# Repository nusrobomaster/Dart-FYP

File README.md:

# 🎯 FYP Dart Launcher (RoboMaster Competition)

This repository hosts the STM32 firmware for our Final Year Project (FYP), which focuses on building the **dart launcher subsystem** for the NUS RoboMaster competition robot. The project is developed and maintained using **STM32CubeIDE** with the DEV A environment, ensuring consistent toolchain and configuration across all team members.

## 🚀 Getting Started (STM32CubeIDE + DEV BOARD A)
Clone this repo and set this repo as your Workspace in stm32cubeide

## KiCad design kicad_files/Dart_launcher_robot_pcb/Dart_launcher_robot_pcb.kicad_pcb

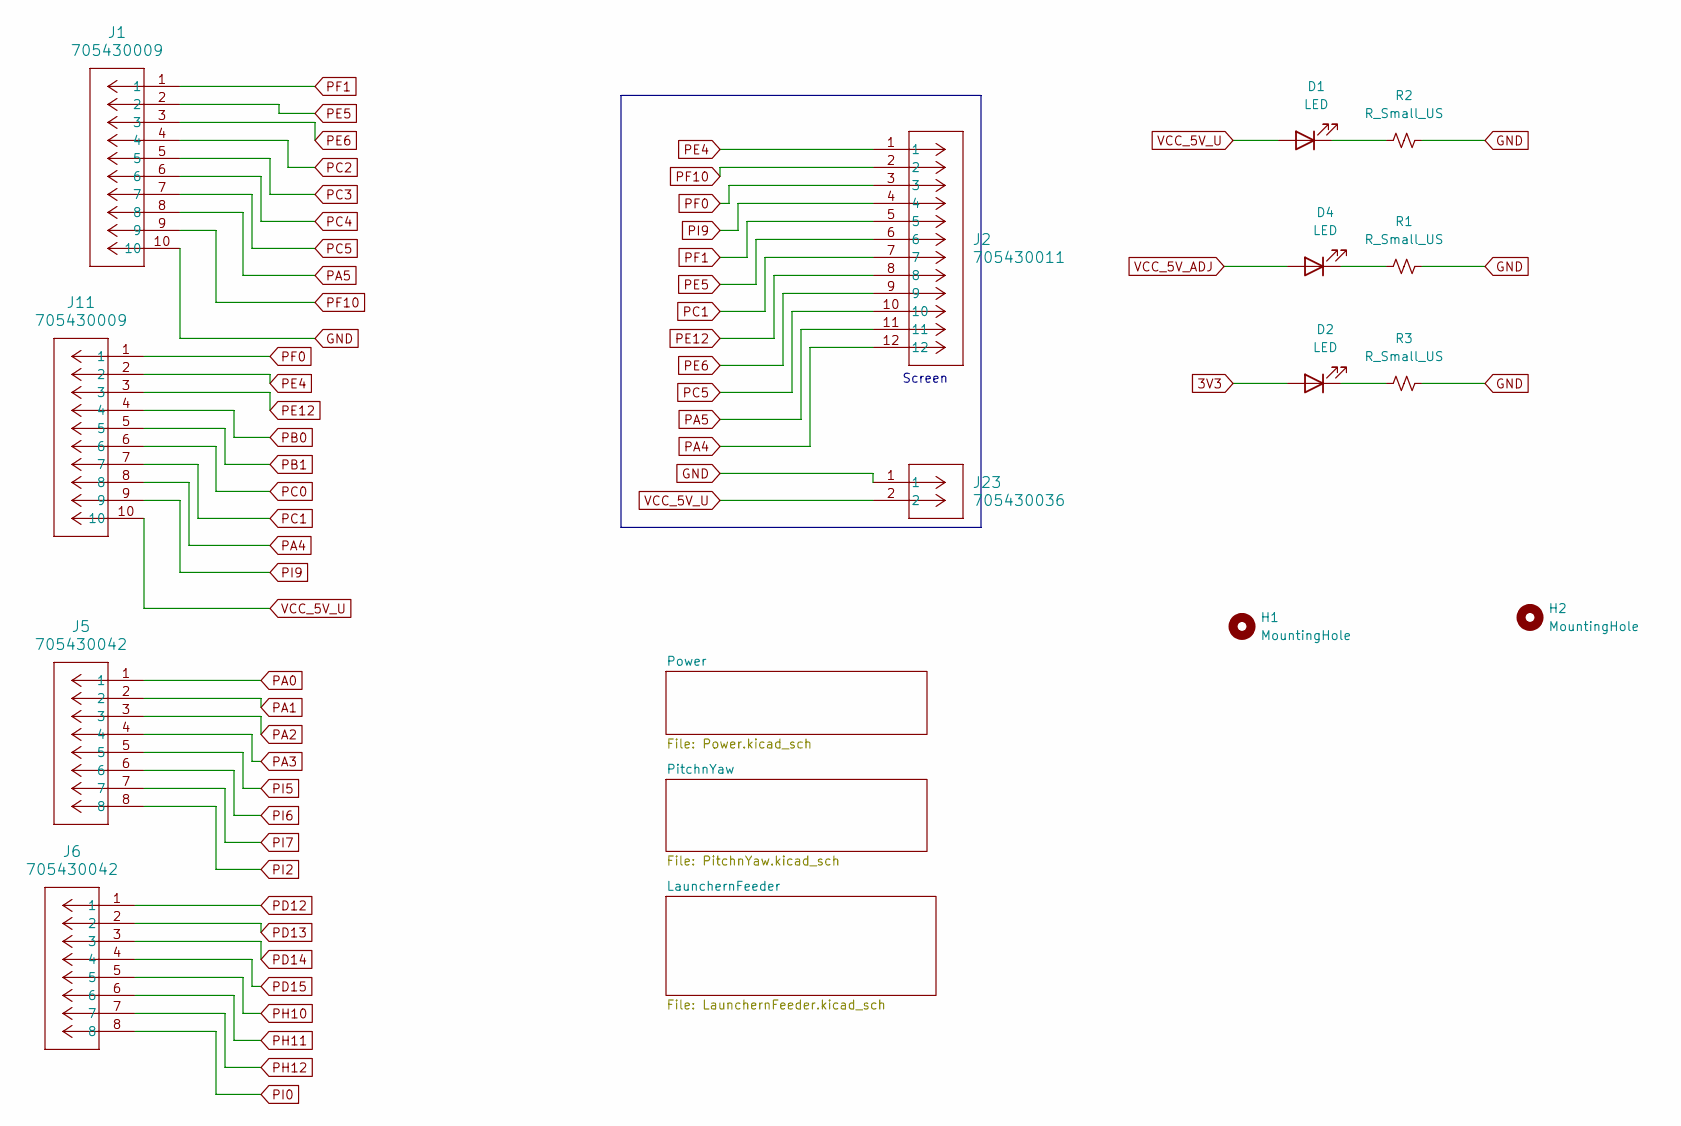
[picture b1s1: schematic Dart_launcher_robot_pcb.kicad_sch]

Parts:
D1, D2, D4: LED; LED_0805_2012Metric_Pad1.15x1.40mm_HandSolder
H1, H2: MountingHole; MountingHole_3.2mm_M3
J1, J11: 705430009; CONN_SDA-70543-xxxx_10_MOL
J2: 705430011; CONN_SDA-70543-xxxx_12_MOL
J5, J6: 705430042; CONN_SDA-70543-xxxx_08_MOL
J23: 705430036; CONN_SDA-70543-xxxx_02_MOL
R1, R2, R3: R_Small_US; R_0603_1608Metric_Pad0.98x0.95mm_HandSolder

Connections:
3V3: D2.2 (A); also elsewhere on the board
GND: J1.10, J23.1, R1.2, R2.2, R3.2; also elsewhere on the board
unnamed: D1.1 (K), R2.1
unnamed: D2.1 (K), R3.1
unnamed: D4.1 (K), R1.1
PA0: J5.1; also elsewhere on the board
PA1: J5.2; also elsewhere on the board
PA2: J5.3; also elsewhere on the board
PA3: J5.4; also elsewhere on the board
PA4: J2.12, J11.8
PA5: J1.8, J2.11
PB0: J11.4; also elsewhere on the board
PB1: J11.5; also elsewhere on the board
PC0: J11.6; also elsewhere on the board
PC1: J2.7, J11.7
PC2: J1.4
PC3: J1.5; also elsewhere on the board
PC4: J1.6; also elsewhere on the board
PC5: J1.7, J2.10
PD12: J6.1; also elsewhere on the board
PD13: J6.2; also elsewhere on the board
PD14: J6.3; also elsewhere on the board
PD15: J6.4; also elsewhere on the board
PE4: J2.1, J11.2
PE5: J1.2, J2.6
PE6: J1.3, J2.9
PE12: J2.8, J11.3
PF0: J2.3, J11.1
PF1: J1.1, J2.5
PF10: J1.9, J2.2
PH10: J6.5
PH11: J6.6
PH12: J6.7; also elsewhere on the board
PI0: J6.8; also elsewhere on the board
PI2: J5.8
PI5: J5.5; also elsewhere on the board
PI6: J5.6
PI7: J5.7
PI9: J2.4, J11.9
VCC_5V_ADJ: D4.2 (A); also elsewhere on the board
VCC_5V_U: D1.2 (A), J11.10, J23.2

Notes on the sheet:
Screen

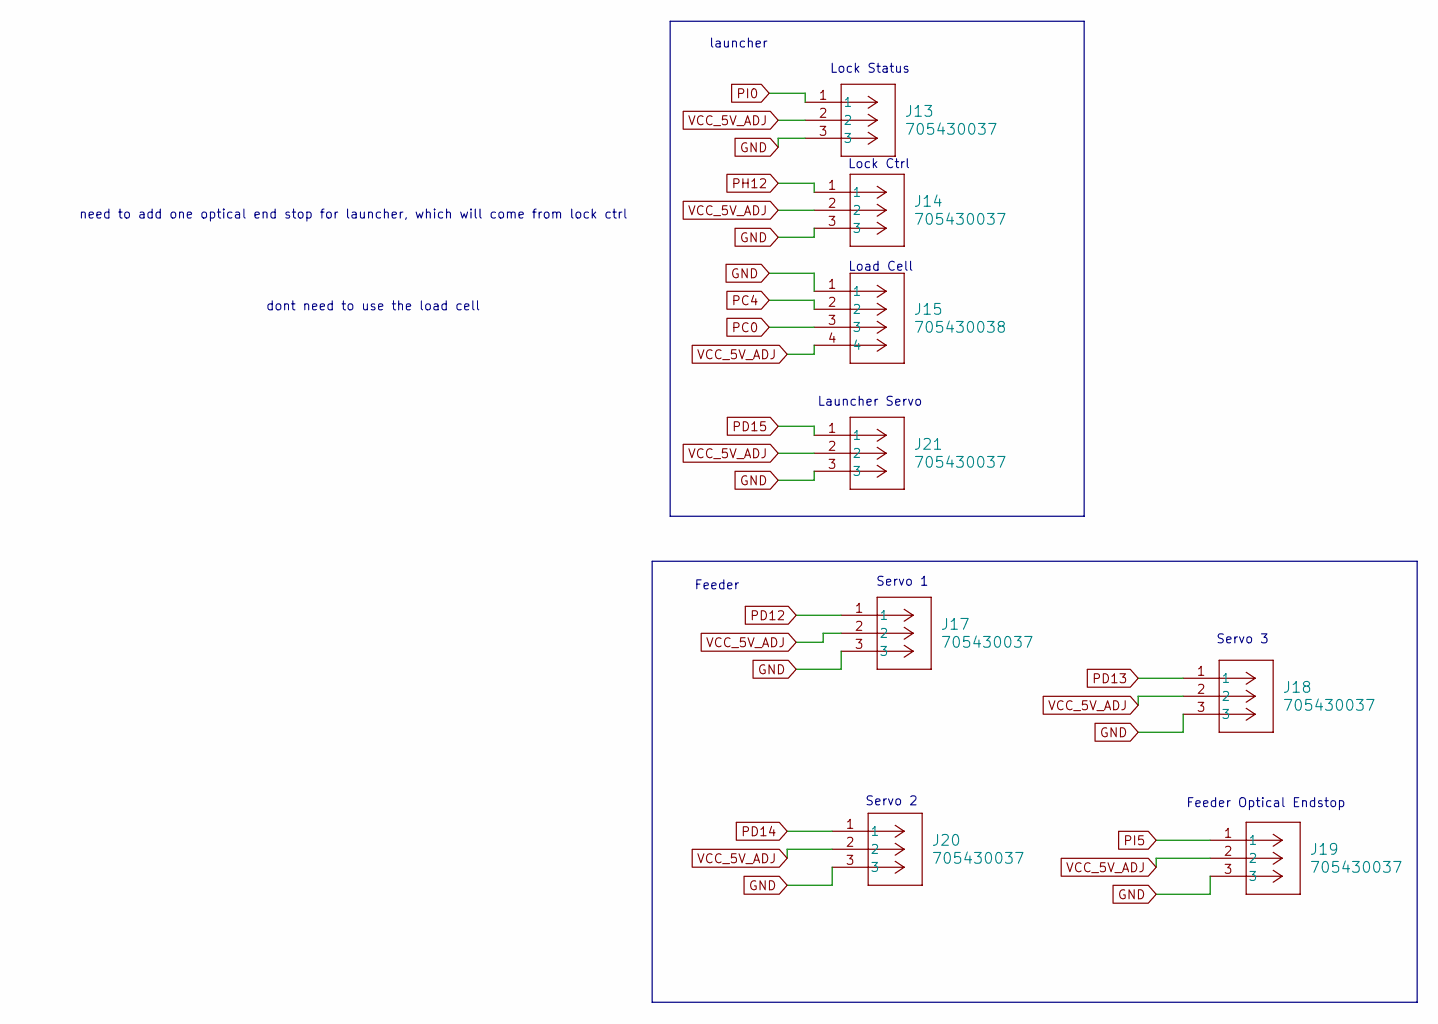
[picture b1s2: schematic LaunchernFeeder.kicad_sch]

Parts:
J13, J14, J17, J18, J19, J20, J21: 705430037; CONN_SDA-70543-xxxx_03_MOL
J15: 705430038; CONN_SDA-70543-xxxx_04_MOL

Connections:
GND: J13.3, J14.3, J15.1, J17.3, J18.3, J19.3, J20.3, J21.3; also elsewhere on the board
PC0: J15.3; also elsewhere on the board
PC4: J15.2; also elsewhere on the board
PD12: J17.1; also elsewhere on the board
PD13: J18.1; also elsewhere on the board
PD14: J20.1; also elsewhere on the board
PD15: J21.1; also elsewhere on the board
PH12: J14.1; also elsewhere on the board
PI0: J13.1; also elsewhere on the board
PI5: J19.1; also elsewhere on the board
VCC_5V_ADJ: J13.2, J14.2, J15.4, J17.2, J18.2, J19.2, J20.2, J21.2; also elsewhere on the board

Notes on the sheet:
Launcher Servo
Lock Ctrl
Servo 3
need to add one optical end stop for launcher, which will come from lock ctrl
launcher
Lock Status
Feeder
Servo 2
dont need to use the load cell
Load Cell
Servo 1
Feeder Optical Endstop

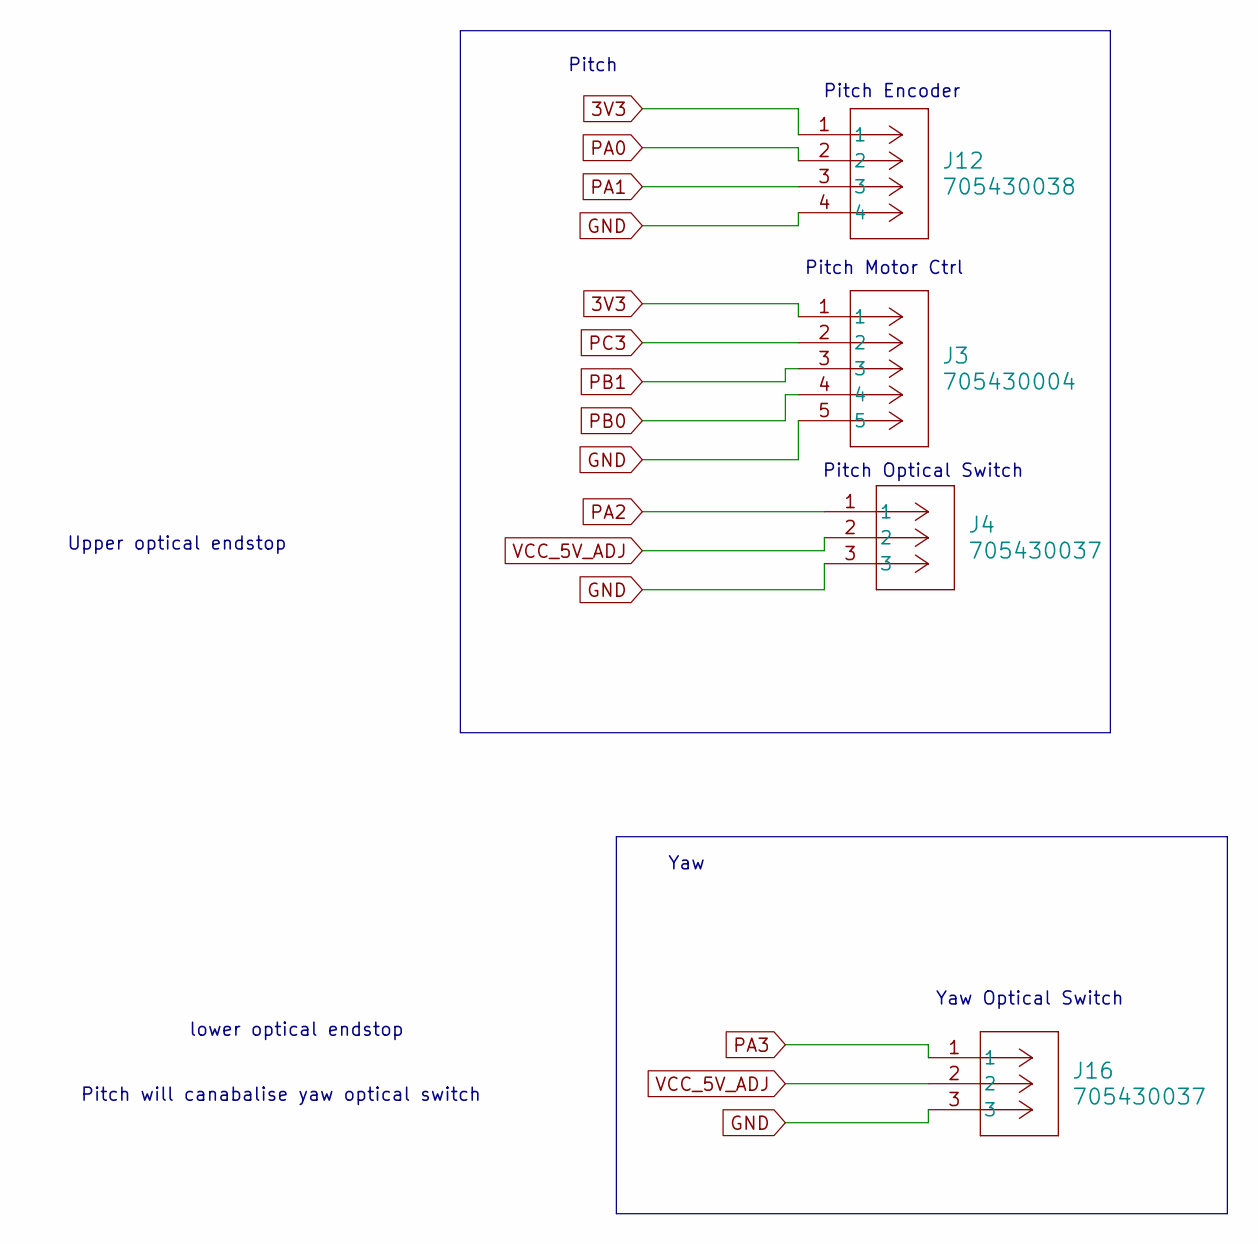
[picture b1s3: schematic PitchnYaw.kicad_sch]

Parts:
J3: 705430004; CONN_SDA-70543-xxxx_05_MOL
J4, J16: 705430037; CONN_SDA-70543-xxxx_03_MOL
J12: 705430038; CONN_SDA-70543-xxxx_04_MOL

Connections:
3V3: J3.1, J12.1; also elsewhere on the board
GND: J3.5, J4.3, J12.4, J16.3; also elsewhere on the board
PA0: J12.2; also elsewhere on the board
PA1: J12.3; also elsewhere on the board
PA2: J4.1; also elsewhere on the board
PA3: J16.1; also elsewhere on the board
PB0: J3.4; also elsewhere on the board
PB1: J3.3; also elsewhere on the board
PC3: J3.2; also elsewhere on the board
VCC_5V_ADJ: J4.2, J16.2; also elsewhere on the board

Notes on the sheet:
Pitch
lower optical endstop
Pitch Encoder
Pitch Motor Ctrl
Yaw
Upper optical endstop
Yaw Optical Switch
Pitch Optical Switch
Pitch will canabalise yaw optical switch

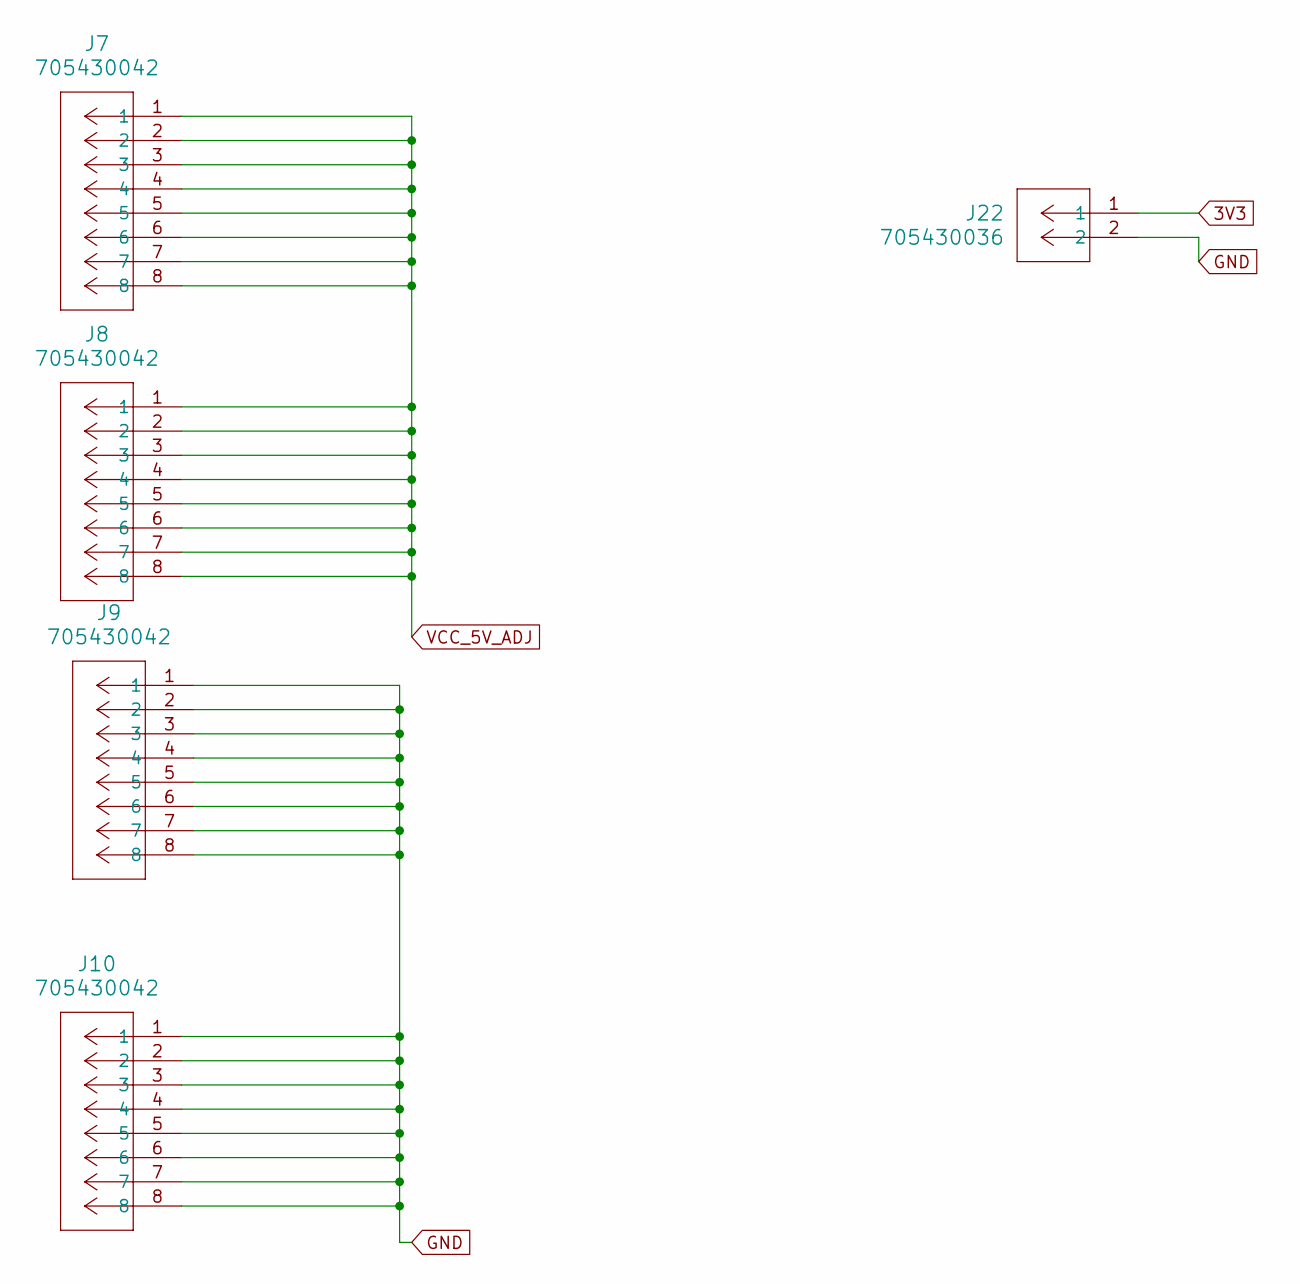
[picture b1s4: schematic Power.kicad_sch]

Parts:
J7, J8, J9, J10: 705430042; CONN_SDA-70543-xxxx_08_MOL
J22: 705430036; CONN_SDA-70543-xxxx_02_MOL

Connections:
3V3: J22.1; also elsewhere on the board
GND: J9.1, J9.2, J9.3, J9.4, J9.5, J9.6, J9.7, J9.8, J10.1, J10.2, J10.3, J10.4, J10.5, J10.6, J10.7, J10.8, J22.2; also elsewhere on the board
VCC_5V_ADJ: J7.1, J7.2, J7.3, J7.4, J7.5, J7.6, J7.7, J7.8, J8.1, J8.2, J8.3, J8.4, J8.5, J8.6, J8.7, J8.8; also elsewhere on the board

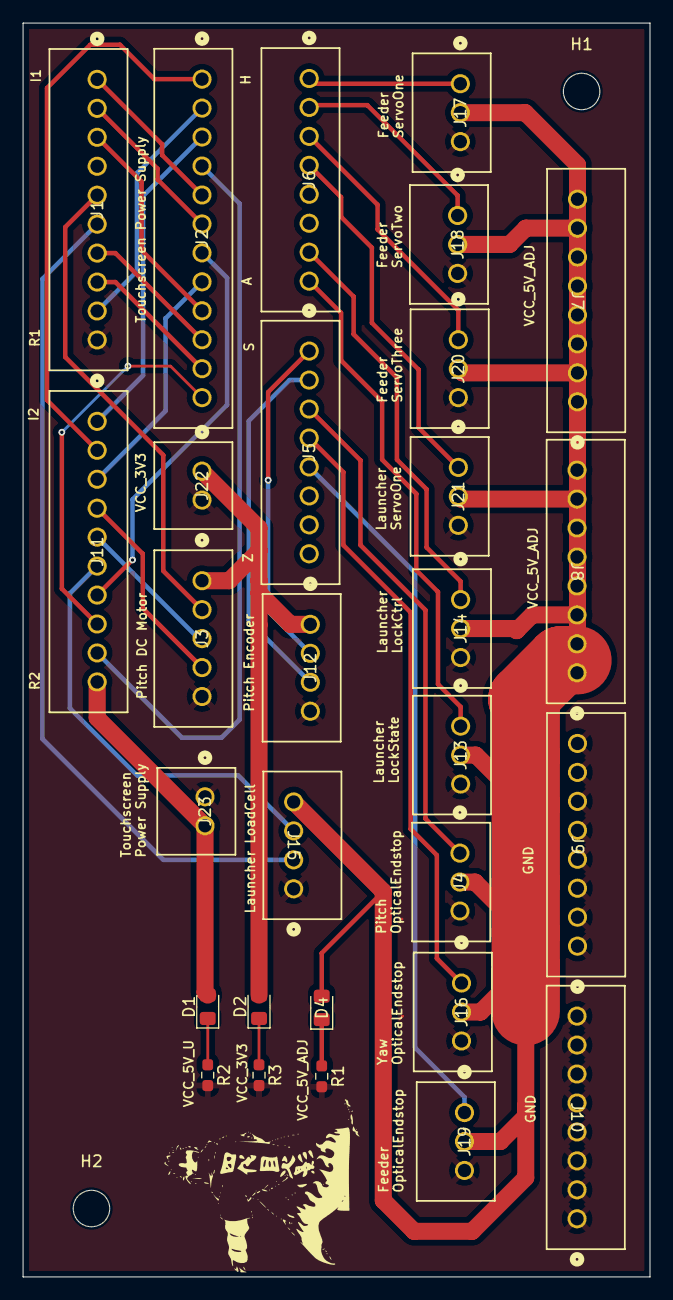
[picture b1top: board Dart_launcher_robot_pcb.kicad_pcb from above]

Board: 2 copper layers, 55.0 x 110.0 mm, 31 parts (0 on the bottom side), 35 nets.

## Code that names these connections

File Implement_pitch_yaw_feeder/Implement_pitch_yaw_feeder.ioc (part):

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Mcu.Name=STM32F427I(G-I)Hx
Mcu.Package=UFBGA176
Mcu.UserName=STM32F427IIHx
PA0/WKUP.Signal=S_TIM2_CH1_ETR
PA1.Signal=S_TIM2_CH2
PA11.Mode=Device_Only
PA11.Signal=USB_OTG_FS_DM
PA12.Mode=Device_Only
PA12.Signal=USB_OTG_FS_DP
PA13.Mode=Serial_Wire
PA13.Signal=SYS_JTMS-SWDIO
PA14.Mode=Serial_Wire
PA14.Signal=SYS_JTCK-SWCLK
PA2.GPIOParameters=GPIO_PuPd,GPIO_ModeDefaultEXTI
PA2.GPIO_ModeDefaultEXTI=GPIO_MODE_IT_RISING
PA2.GPIO_PuPd=GPIO_PULLDOWN
PA2.Signal=GPXTI2
PA3.GPIOParameters=GPIO_PuPd
PA3.GPIO_PuPd=GPIO_PULLDOWN
PA3.Signal=GPXTI3
PA4.Signal=GPIO_Output
PA5.Signal=GPIO_Output
PB0.Signal=S_TIM3_CH3
PB1.Signal=GPIO_Output
PB6.Mode=Asynchronous
PB6.Signal=USART1_TX
PB7.Mode=Asynchronous
PB7.Signal=USART1_RX
PC1.Signal=GPIO_Output
PC2.Signal=GPIO_Output
PC3.Signal=GPIO_Output
PC5.Signal=GPIO_Output
PD0.Mode=CAN_Activate
PD0.Signal=CAN1_RX
PD1.Mode=CAN_Activate
PD1.Signal=CAN1_TX
PD12.Signal=S_TIM4_CH1
PD13.Signal=S_TIM4_CH2
PD14.Signal=S_TIM4_CH3
PD15.Signal=S_TIM4_CH4
PE12.Mode=Full_Duplex_Master
PE12.Signal=SPI4_SCK
PE3.Signal=GPIO_Output
PE4.GPIOParameters=PinState
PE4.PinState=GPIO_PIN_SET
PE4.Signal=GPIO_Output
PE5.Mode=Full_Duplex_Master
PE5.Signal=SPI4_MISO
PE6.Mode=Full_Duplex_Master
PE6.Signal=SPI4_MOSI
PF0.Mode=I2C
PF0.Signal=I2C2_SDA
PF1.Mode=I2C
PF1.Signal=I2C2_SCL
PF10.Signal=GPXTI10
PG1.Signal=GPIO_Output
PH0/OSC_IN.Mode=HSE-External-Oscillator
PH0/OSC_IN.Signal=RCC_OSC_IN
PH1/OSC_OUT.Mode=HSE-External-Oscillator
PH1/OSC_OUT.Signal=RCC_OSC_OUT
PH12.GPIOParameters=GPIO_PuPd
PH12.GPIO_PuPd=GPIO_PULLDOWN
PH12.Signal=GPXTI12
PI0.GPIOParameters=GPIO_PuPd
PI0.GPIO_PuPd=GPIO_PULLUP
PI0.Signal=GPIO_Input
PI5.GPIOParameters=GPIO_PuPd,GPIO_ModeDefaultEXTI
PI5.GPIO_ModeDefaultEXTI=GPIO_MODE_IT_RISING
PI5.GPIO_PuPd=GPIO_PULLDOWN
PI5.Signal=GPXTI5
PI6.GPIOParameters=GPIO_ModeDefaultEXTI
PI6.GPIO_ModeDefaultEXTI=GPIO_MODE_IT_RISING_FALLING
PI6.Signal=GPXTI6
PI9.Signal=GPIO_Output
RCC.HSE_VALUE=12000000
RCC.SYSCLKFreq_VALUE=168000000
RCC.SYSCLKSource=RCC_SYSCLKSOURCE_PLLCLK
board=custom

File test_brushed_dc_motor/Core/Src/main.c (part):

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//======================================= LCD Interface ===========================================//
// The module defaults to SPI mode
// LCD Module STM32 MCU
// SDI (MOSI) -> PE6 // SPI data write
// SDO (MISO) -> PE5 // SPI data read (optional)
//======================================= LCD Interface ===========================================//
// LCD Module STM32 MCU
// LED -> PC1 // Backlight control (or tie to 5V / 3.3V)
// SCK -> PE12 // SPI clock
// LCD_RS -> PC5 // Data / Command select
// LCD_RST -> PA5 // LCD reset
// LCD_CS -> PA4 // Chip select
//===================================== Touch (Optional) ==========================================//
// If touch is not used, these pins can be left unconnected
// Touch Module STM32 MCU
// CTP_INT -> PF10 // Touch interrupt
// CTP_SDA -> PF0 // I2C data
// CTP_RST -> PI9 // Touch reset
// CTP_SCL -> PF1 // I2C clock
//======================================= HX711 Load Cell =========================================//
// HX711 STM32 MCU
// SCLK -> PC0 // HX711 clock
// DOUT -> PC4 // HX711 data output
//==================================== Electronic Lock ============================================//
// Lock Signal STM32 MCU
// Lock_Input -> PA0 // Lock status / sense input
// Lock_Output -> PA1 // Lock / unlock control output


// PC3 is  pitch down
// PB1 is  pitch up
// PA2 is pitch upper optical endstop
// PA3 is pitch lower optical endstop

// PI0 is for lock status
// PH12 is for launcher optical endstop
// PD15 is for  launcher servo to release the dart

//D12 is for feeder servo 1
//D13 is for feeder servo 2
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  /*Configure GPIO pin Output Level */
  HAL_GPIO_WritePin(GPIOB, GPIO_PIN_1|GPIO_PIN_0, GPIO_PIN_RESET);

  /*Configure GPIO pins : PE3 PE4 */
  GPIO_InitStruct.Pin = GPIO_PIN_3|GPIO_PIN_4;
  GPIO_InitStruct.Mode = GPIO_MODE_OUTPUT_PP;
  GPIO_InitStruct.Pull = GPIO_NOPULL;
  GPIO_InitStruct.Speed = GPIO_SPEED_FREQ_LOW;
  HAL_GPIO_Init(GPIOE, &GPIO_InitStruct);

  /*Configure GPIO pins : PI7 PI9 */
  GPIO_InitStruct.Pin = GPIO_PIN_7|GPIO_PIN_9;
  GPIO_InitStruct.Mode = GPIO_MODE_OUTPUT_PP;
  GPIO_InitStruct.Pull = GPIO_NOPULL;
  GPIO_InitStruct.Speed = GPIO_SPEED_FREQ_LOW;
  HAL_GPIO_Init(GPIOI, &GPIO_InitStruct);

  /*Configure GPIO pin : PF10 */
  GPIO_InitStruct.Pin = GPIO_PIN_10;
  GPIO_InitStruct.Mode = GPIO_MODE_OUTPUT_PP;
  GPIO_InitStruct.Pull = GPIO_NOPULL;
  GPIO_InitStruct.Speed = GPIO_SPEED_FREQ_LOW;
  HAL_GPIO_Init(GPIOF, &GPIO_InitStruct);

  /*Configure GPIO pins : PC0 PC1 PC2 PC3
                           PC5 */
  GPIO_InitStruct.Pin = GPIO_PIN_0|GPIO_PIN_1|GPIO_PIN_2|GPIO_PIN_3
                          |GPIO_PIN_5;
  GPIO_InitStruct.Mode = GPIO_MODE_OUTPUT_PP;
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  GPIO_InitStruct.Speed = GPIO_SPEED_FREQ_LOW;
  HAL_GPIO_Init(GPIOG, &GPIO_InitStruct);

  /*Configure GPIO pins : PA4 PA5 */
  GPIO_InitStruct.Pin = GPIO_PIN_4|GPIO_PIN_5;
  GPIO_InitStruct.Mode = GPIO_MODE_OUTPUT_PP;
  GPIO_InitStruct.Pull = GPIO_NOPULL;
  GPIO_InitStruct.Speed = GPIO_SPEED_FREQ_LOW;
  HAL_GPIO_Init(GPIOA, &GPIO_InitStruct);

  /*Configure GPIO pin : PC4 */
  GPIO_InitStruct.Pin = GPIO_PIN_4;
  GPIO_InitStruct.Mode = GPIO_MODE_INPUT;
  GPIO_InitStruct.Pull = GPIO_NOPULL;
  HAL_GPIO_Init(GPIOC, &GPIO_InitStruct);

  /*Configure GPIO pins : PB1 PB0 */
  GPIO_InitStruct.Pin = GPIO_PIN_1|GPIO_PIN_0;
  GPIO_InitStruct.Mode = GPIO_MODE_OUTPUT_PP;
  GPIO_InitStruct.Pull = GPIO_NOPULL;
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
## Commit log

2025-09-23 Initialize all file
2025-09-23 Update README.md
    DEVA - > DEV A
2025-09-23 Create README.md for one project
2025-09-23 Add files via upload
    for readme file
2025-09-23 Update README.md
    add images to readme
2025-10-14 Implement a screeen view of real life weight sensor data
2025-10-15 implement prototype2
2025-10-15 Implemented the FSM for motor moving
2025-11-13 Add jekyll
2025-11-13 I trying this .md bs
2025-11-13 try 2
2025-11-13 try 3
2025-11-13 try 4
2025-11-13 adding content 1, for dart robot yaw
2025-11-13 adding content 2, for dart robot pitch
2025-11-14 try one image
2025-11-14 update that image to center
2025-11-14 change to html to achieve center alignment
2025-11-14 fixing html
2025-11-14 fixing html 2
2025-11-14 html fix 3
2025-11-14 Yeeted all yaw pictures and captions in
2025-11-14 fixing html 4
2025-11-14 Update Projectile - Mechanical Design.md
    shyam did dis try
2025-11-14 Added appendix page and more images
2025-11-14 OCD images change
2025-11-14 Fix again (1)
2025-11-14 shyam addpics
2025-11-14 pics
2025-11-14 Base page started
2025-11-14 Add in manpower alloc, with drop down
2025-11-14 Fixing pages
2025-11-14 Fixing pages 2
2025-11-14 Fixing pages 3
2025-11-14 Fixing pages 4
2025-11-14 Fixing pages 5
2025-11-14 Added more drop downs
2025-11-14 swapping in jianwen pages
2025-11-14 VJ Intro added
2025-11-14 barry and shyam intro added, left jobscope portion unsure to add in
2025-11-14 trying katex
2025-11-14 trying katex 2
2025-11-14 trying the font shit, times new roman
2025-11-14 change font to arial, font size to 20 px
2025-11-14 fixing font
2025-11-14 many changes, captions made smaller
2025-11-14 for the math nerds
2025-11-14 add faces
2025-11-14 face fix 1
2025-11-14 face fix 2
2025-11-14 face fix 3
2025-11-14 face fix 4
2025-11-14 face fix 5
2025-11-14 small edits for dart robot subsystems page
2025-11-14 Redirect Index to go to Introduction
2025-11-14 fix links 1
2025-11-14 fix links 2
2025-11-14 edit page title
2025-11-14 small fix for title
2025-11-14 small fix 2
2025-11-14 i forgot to save a file hais
2025-11-14 sorry for crashing
2025-11-15 push launcher
2025-11-15 projectile add
2025-11-15 glider
2025-11-15 thorn
2025-11-15 glider p
2025-11-15 shyamupdate
2025-11-15 trident
2025-11-15 shyamnew
2025-11-15 new2
2025-11-15 Fix report structure and added some projectile elec images
2025-11-15 Add dart robot elec and software
2025-11-15 small change on my image
2025-11-15 new3
2025-11-15 testing img
2025-11-15 try to fix images
2025-11-15 shayms image fixed
2025-11-15 jian wen fix image
2025-11-15 fix again jian wen
2025-11-15 fix image for relevant files
2025-11-15 fix elec robot nav position
2025-11-15 fix nav and perma link
2025-11-15 fix grandparent and parent
2025-11-15 add 6 7
2025-11-15 add logo to table
2025-11-15 Add video for user journey
2025-11-15 change till 7.1.3 for launcher electrical & software
2025-11-15 change title of page for robo elec and software
2025-11-15 wtf is this
2025-11-15 changed figure numbers
2025-11-15 changed appendix stuff
2025-11-15 add to elect and soft gui lib
2025-11-15 changes again
2025-11-15 changes again 2
2025-11-15 remove index.md
2025-11-15 remove index.md 2
2025-11-15 remove index.md 3
2025-11-15 more text written for testing and code development
2025-11-15 remove index.md 4
2025-11-15 remove temp repo
2025-11-15 fixed hyperlinks, added in project plan words cause everyone forgot about it
2025-11-15 Add more to the dart robot electrical and software
2025-11-15 change config file to rename template file to a asi repo
2025-11-15 make changes to share dart robot and projectiles
2025-11-15 Do projectile elec and software
2025-11-15 last part video
2025-11-15 new4
2025-11-15 new5
2025-11-16 added functionality table
2025-11-16 more edits cause wtf is this
2025-11-16 new7
2025-11-16 fix numbering and nomenclature of headings
2025-11-16 changed figure labels
2025-11-16 base structure figure numbers fixed
2025-11-16 change 1 need change again
2025-11-16 end of this change
2025-11-16 changed the dart system page to have fking TRANSITION from functionality table
2025-11-16 add headings to the robot and projectile pages to make it look less like a rushed job
2025-11-16 changes to projectile page
2025-11-16 further changes with links for projectile and robot main pages
2025-11-16 change again for robot main page
2025-11-16 more changes to the robot and projectile main pages
2025-11-16 cb more changes
2025-11-16 spelling mistakes
2025-11-16 changing shitty elect and software robot
2025-11-16 more shittty elect and software report to change
2025-11-16 more stuff to fix
2025-11-16 pushy push push
2025-11-16 Add Base elec stuff
2025-11-16 fix base spec table
2025-11-16 Appendix number fix
2025-11-16 Make changes to elect
2025-11-16 added stuff to base
2025-11-16 added stuff to base 2
2025-11-16 no more
2025-11-16 Life is tough
2025-11-16 Add some appendix for intro
2025-11-16 VJ is a gooning god
2025-11-16 Add appendix for projectile elec
2025-11-16 video for base diff intro
2025-11-16 base diff video intro
2025-11-16 add protyping and testing for projectile elec
2025-11-16 fix formatting for projectile elc
2025-11-16 Modify reference and its order
2025-11-16 i dc
2025-11-16 fix references
2025-11-16 add clicker links
2025-11-16 fix links
2025-11-17 tough bro
2025-11-17 numbering error for module testing and code dev
2025-12-01 DM motor Dev A
    some how it works
2025-12-03 Fix initialization for damiao motor
    Found out that the intialization is too fast resulting in no enabling of motor
2025-12-09 Create new project for testing lvgl and touchscreen
2025-12-10 test m3508 on dev c
2025-12-18 Should have split this into multiple commits
    dm motor project has step based rpm change
    test_LVGL now has touch button capability after the inclusion of indef from lvgl documentation
    test_touch was a test code to try out touchgfx incase lvgl did not suceed
2025-12-26 Implement New Touch LCD Screen
2025-12-26 Implemented new capcitive screen with LVGL
2025-12-26 Created prototype 3
    improvement from 2 is the inclusion of lvgl and the new cap touch screen
2025-12-26 Change from rm motor to dm motors
2025-12-28 created prototype4
    plan is to create the structure of the code
2025-12-28 add briteencoder driver
    task in ioc file can be created as weak
2026-01-13 Test servos
2026-01-14 implemented dc motor control
2026-01-16 Test eez studio flow with lvgl
    made changes to prototype 4
2026-01-16 implement global position
2026-01-16 implement correct mapping of position control
2026-01-17 Implement negative rotations
2026-01-18 Implement feeder code
2026-01-18 Rename project to implement pitch_yaw_feeder
    cleaned up typedefs.h
2026-01-19 Test briterencoder
2026-01-20 Flip screen for vertical reading
2026-01-20 eez studio flow works
2026-01-20 add eez studio flow
2026-01-21 change the structure for code for better integration with eez flow
2026-01-21 kinda working screen
2026-01-21 Screen is working
2026-01-24 Tested optical switch
2026-01-25 implement launcher
2026-01-25 Improved UI for lower space util
2026-01-26 implement launcher state machine
2026-01-27 fix some issues, implement pitch yaw feeder did not update task properly
2026-01-28 clean up code and include #define to ignore ioc file generated uart
2026-01-31 implement test for launcher
2026-02-01 update gitignore to handle kicad
2026-02-05 update gitignore for kicad project
2026-02-05 Add existing kicad file
2026-03-05 pcb design and changes to the pitch_yaw_launcher_code
2026-03-12 the launcher task canabalise the feeder task
    update the frequency of the communication to handle longer cable length
    update the pitch yaw to handle control of all the different type of control method
    update screen to have an auto tab and a rc tab
2026-03-13 Fix usage of can from different task
    implement turn off controller
    change sequence to handle
    handle interrupr
2026-03-14 fix launcher and pitch and yaw
2026-03-14 revert to old remote code
2026-03-14 fixed test_brushed_dc_motor
2026-03-14 fix controller
2026-03-14 handle reading of data from the motor
2026-03-15 update code to go to feeder
2026-03-16 tuning pid
2026-03-17 working code
2026-03-21 code working with feeder
2026-04-08 change made
2026-04-10 Implement error display for yaw and pitch
2026-04-10 yaw control radian yaw read deg
2026-04-10 isolate screen code
2026-04-11 can use this for demo
2026-04-12 extra code to test screen with pitch and yaw individually
2026-04-15 state_machine plus some ui diagram

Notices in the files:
test_brushed_dc_motor/Core/Src/main.c:
Copyright (c) 2025 STMicroelectronics.
All rights reserved.
This software is licensed under terms that can be found in the LICENSE file
